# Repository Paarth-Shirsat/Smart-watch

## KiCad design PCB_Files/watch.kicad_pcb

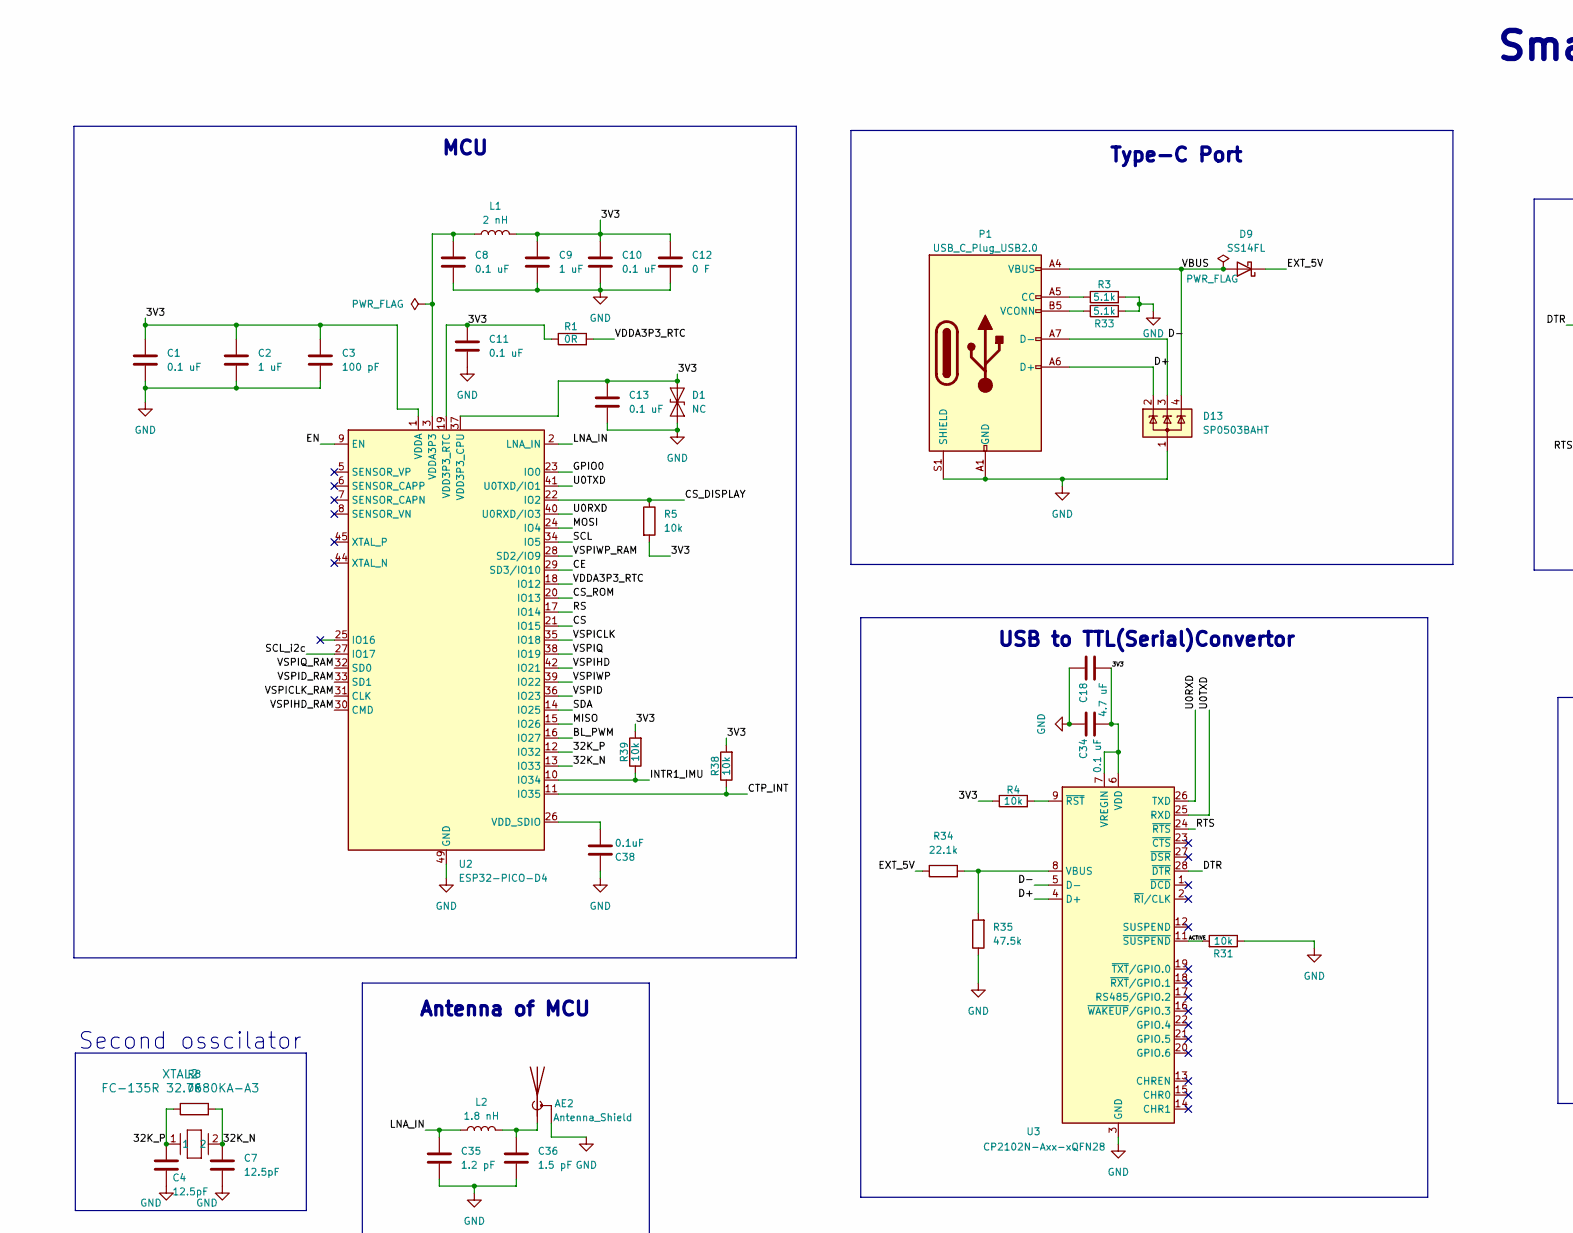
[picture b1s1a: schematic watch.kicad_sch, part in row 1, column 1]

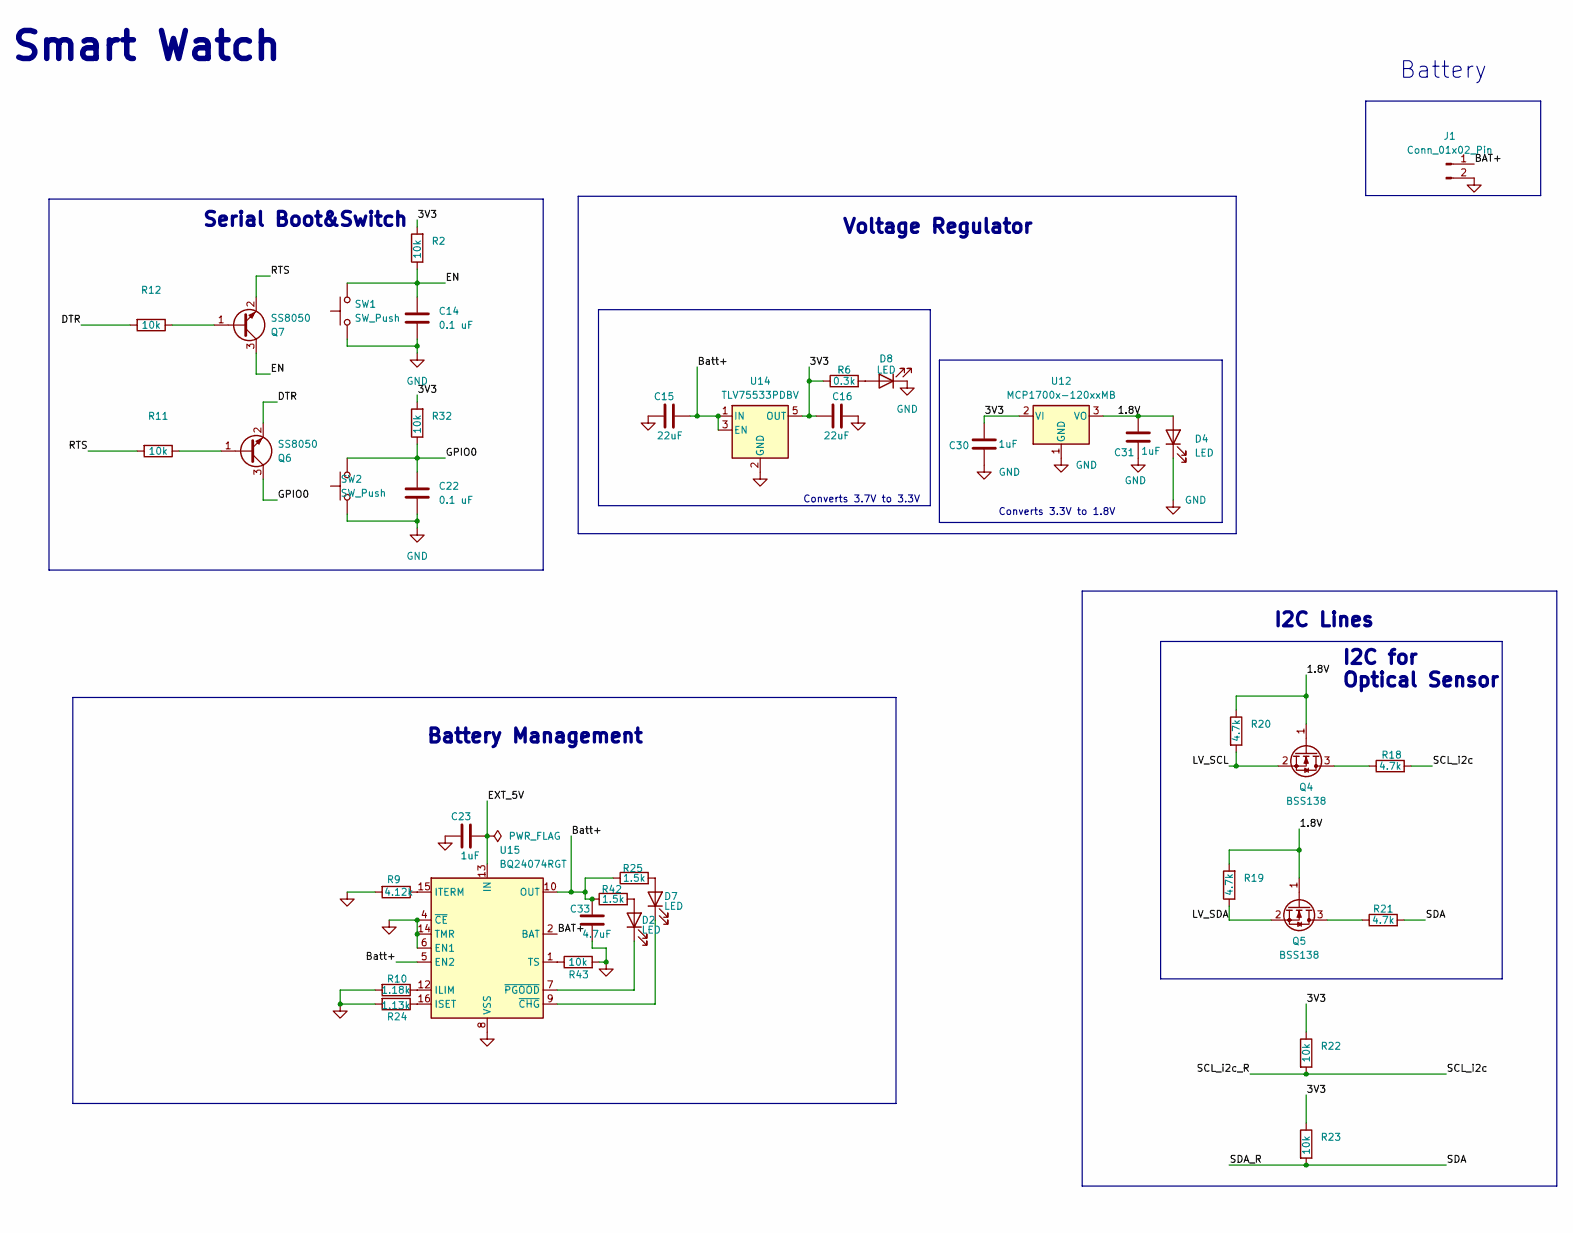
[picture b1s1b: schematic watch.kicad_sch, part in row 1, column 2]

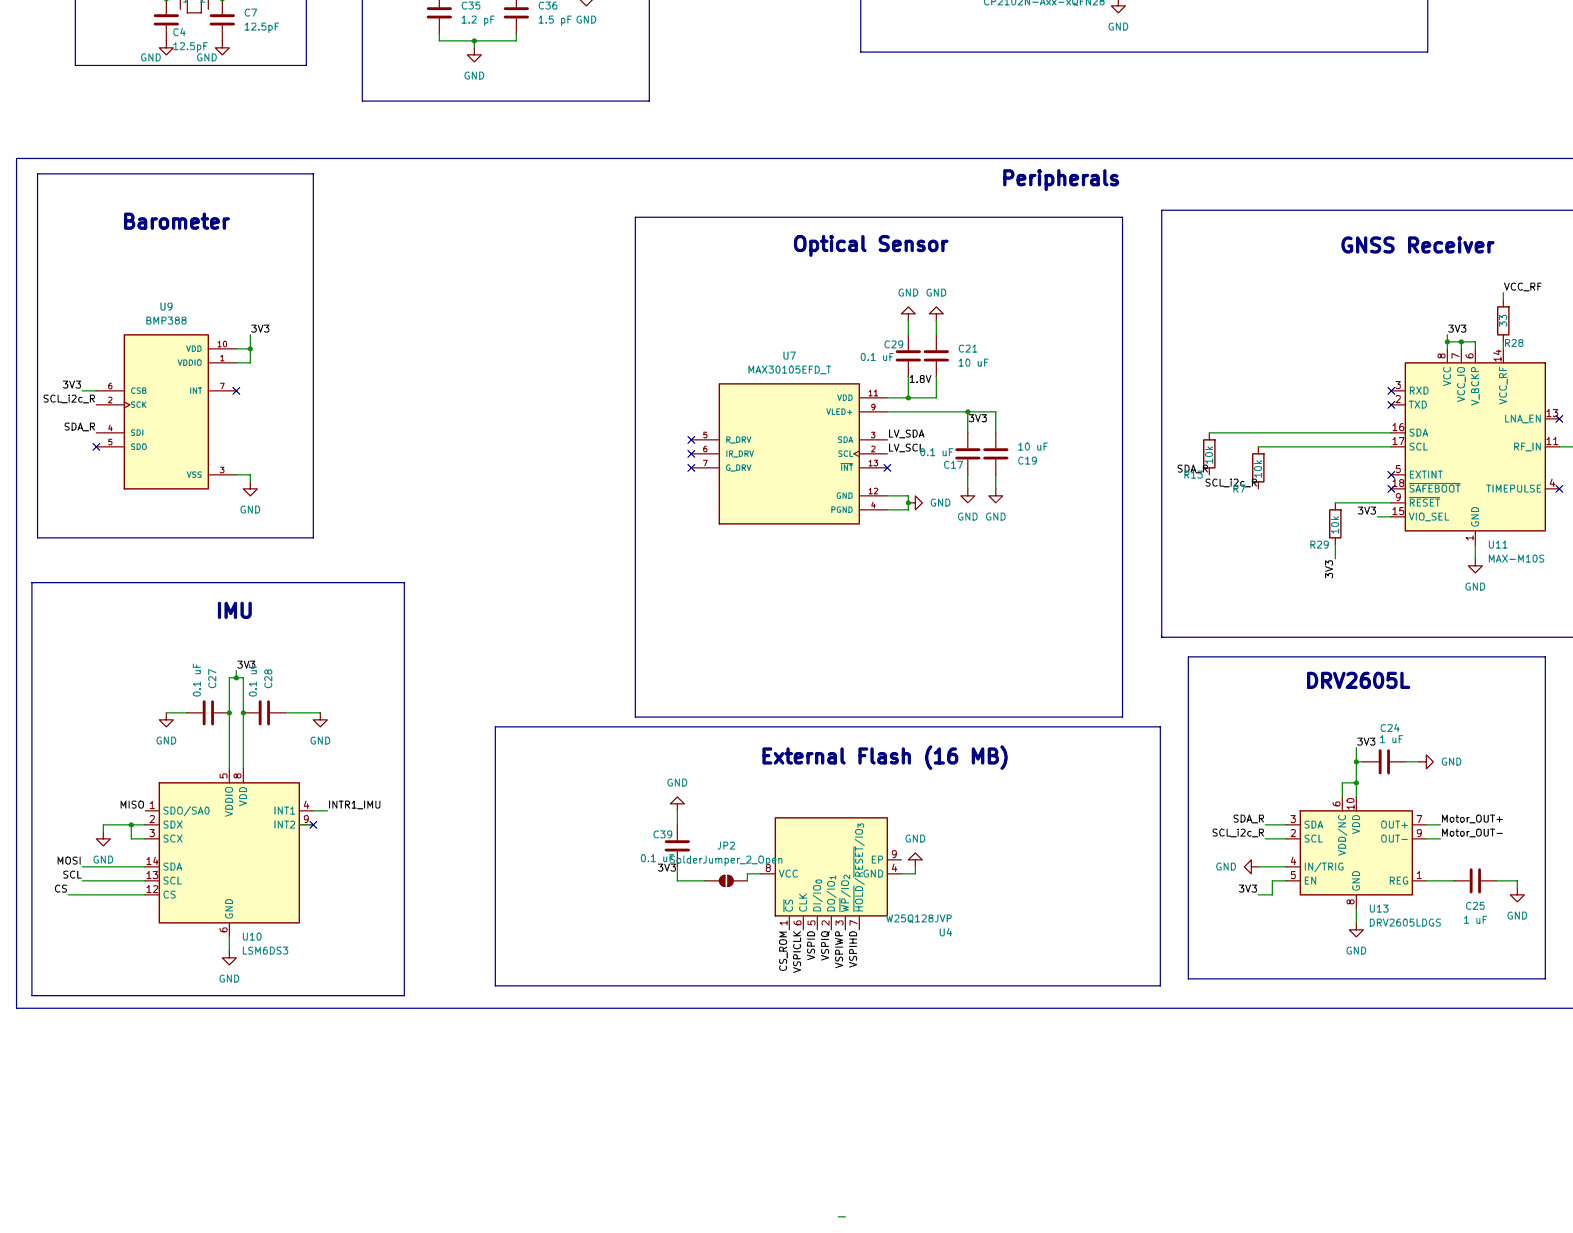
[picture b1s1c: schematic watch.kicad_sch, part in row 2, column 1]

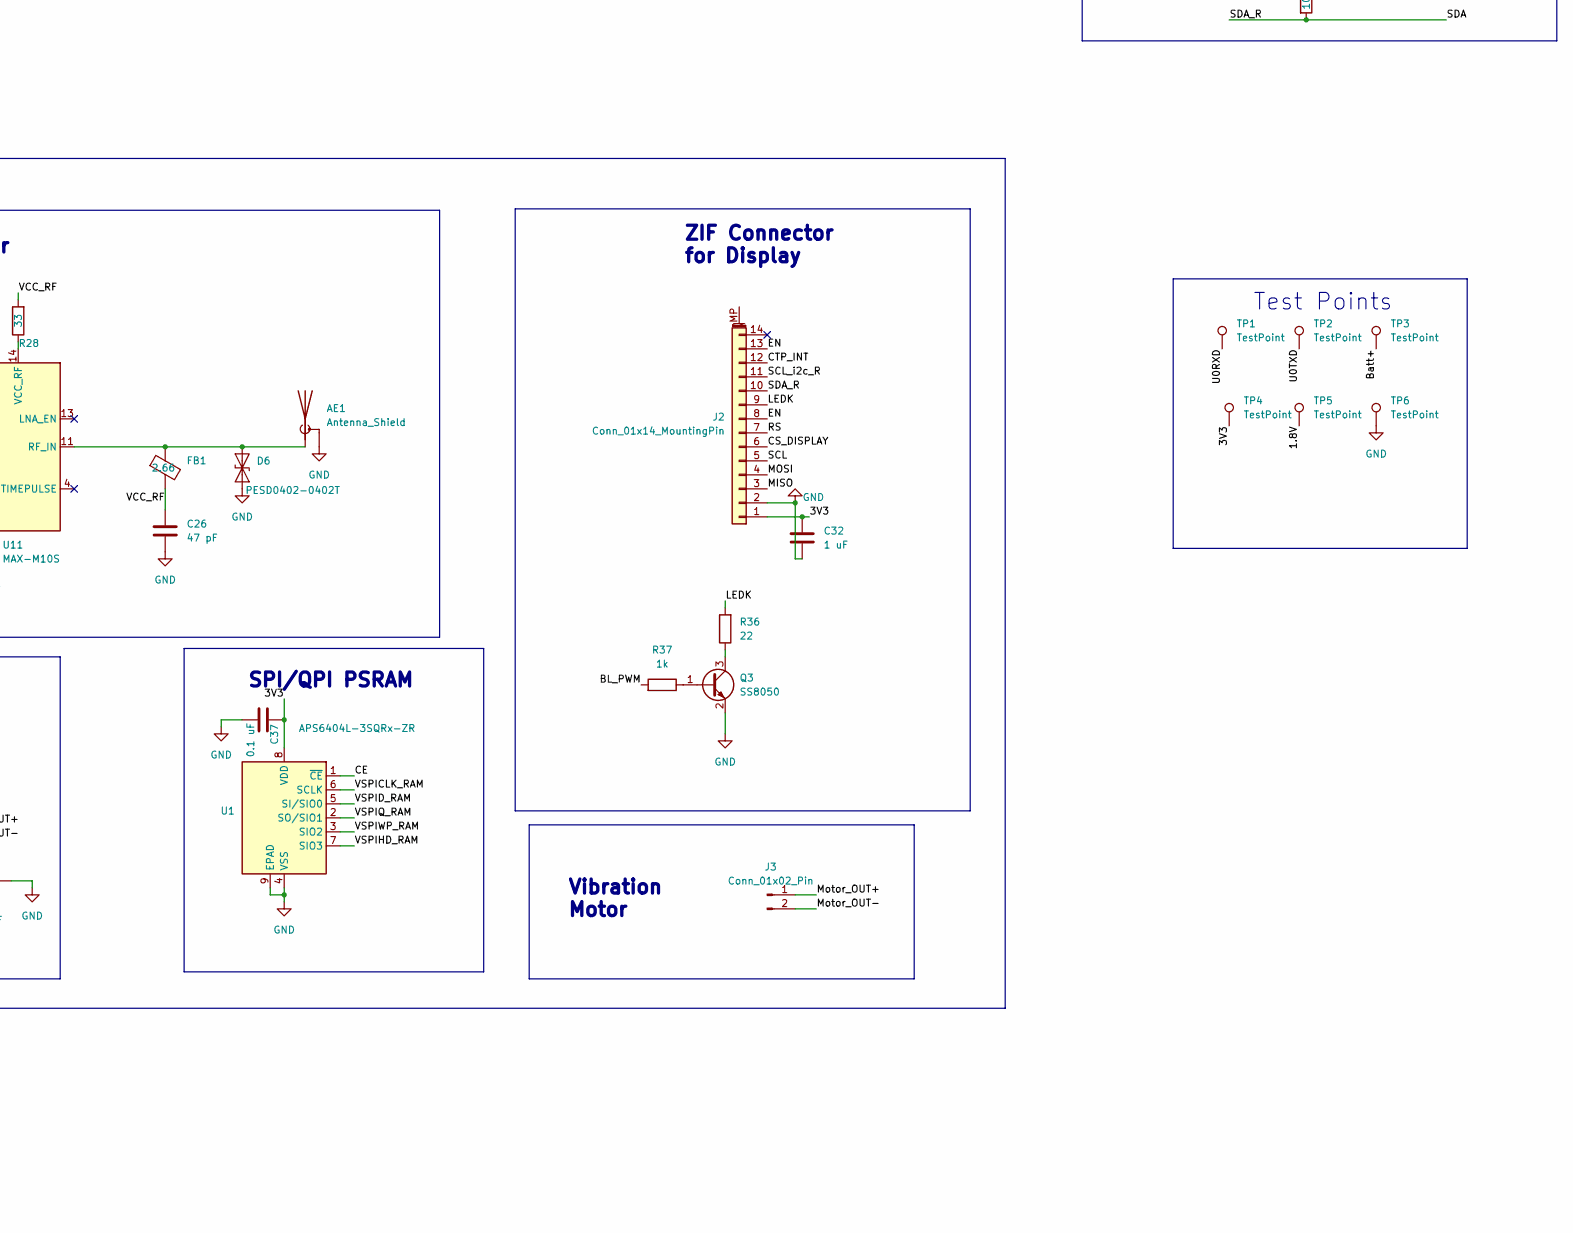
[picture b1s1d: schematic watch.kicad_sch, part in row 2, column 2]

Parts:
AE1, AE2: Antenna_Shield; XCVR_NN03-320
C1, C8, C10, C11, C13, C14, C17, C22, C27, C28, C29, C34, C37, C39: 0.1 uF; C_0603_1608Metric
C2, C9, C24, C25, C32: 1 uF; C_0603_1608Metric
C3: 100 pF; C_0603_1608Metric
C4, C7: 12.5pF; C_0603_1608Metric
C12: 0 F; C_0603_1608Metric
C15, C16: 22uF; C_0603_1608Metric
C18: 4.7 uF; C_0603_1608Metric
C19, C21: 10 uF; C_0603_1608Metric
C23, C30, C31: 1uF; C_0603_1608Metric
C26: 47 pF; C_0402_1005Metric
C33: 4.7uF; C_0603_1608Metric
C35: 1.2 pF; C_0603_1608Metric
C36: 1.5 pF; C_0603_1608Metric
C38: 0.1uF; C_0603_1608Metric
D1: NC; C_0603_1608Metric
D2, D4, D7, D8: LED; LED_0603_1608Metric
D6: PESD0402-0402T; D_SOD-923
D9: SS14FL; D_SOD-123
D13: SP0503BAHT; SOT-143
FB1: 2.66; L_0402_1005Metric
J1: Conn_01x02_Pin; PinHeader_1x02_P1.00mm_Vertical
J2: Conn_01x14_MountingPin; HRS_FH34SRJ-14S-0.5SH_50_
J3: Conn_01x02_Pin; D_0603_1608Metric
JP2: SolderJumper_2_Open; R_0402_1005Metric
L1: 2 nH; L_0603_1608Metric
L2: 1.8 nH; L_0603_1608Metric
P1: USB_C_Plug_USB2.0; USB_C_Receptacle_GCT_USB4105-xx-A_16P_TopMnt_Horizontal
Q3, Q6, Q7: SS8050; SOT-23
Q4, Q5: BSS138; SOT-23
R1, R8: 0R; R_0603_1608Metric
R2, R4, R5, R7, R11, R12, R13, R22, R23, R29, R31, R32, R38, R39, R43: 10k; R_0603_1608Metric
R3, R33: 5.1k; R_0603_1608Metric
R6: 0.3k; R_0603_1608Metric
R9: 4.12k; R_0603_1608Metric
R10: 1.18k; R_0603_1608Metric
R18, R19, R20, R21: 4.7k; R_0603_1608Metric
R24: 1.13k; R_0603_1608Metric
R25, R42: 1.5k; R_0603_1608Metric
R28: 33; R_0402_1005Metric
R34: 22.1k; R_0603_1608Metric
R35: 47.5k; R_0603_1608Metric
R36: 22; R_0603_1608Metric
R37: 1k; R_0603_1608Metric
SW1, SW2: SW_Push; SW_Push_SPST_NO_Alps_SKRK
TP1, TP2, TP3, TP4, TP5, TP6: TestPoint; TestPoint_Pad_D1.0mm
U1: APS6404L-3SQRx-ZR; Winbond_USON-8-1EP_3x2mm_P0.5mm_EP0.2x1.6mm
U2: ESP32-PICO-D4; QFN-48-1EP_7x7mm_P0.5mm_EP5.3x5.3mm
U3: CP2102N-Axx-xQFN28; QFN-28-1EP_5x5mm_P0.5mm_EP3.35x3.35mm
U4: W25Q128JVP; WSON-8-1EP_6x5mm_P1.27mm_EP3.4x4.3mm
U7: MAX30105EFD_T; 14-OESIP
U9: BMP388; PQFN50P200X200X80-10N
U10: LSM6DS3; LGA-14_3x2.5mm_P0.5mm_LayoutBorder3x4y
U11: MAX-M10S; ublox_MAX
U12: MCP1700x-120xxMB; SOT-89-3
U13: DRV2605LDGS; VSSOP-10_3x3mm_P0.5mm
U14: TLV75533PDBV; SOT-23-5
U15: BQ24074RGT; VQFN-16-1EP_3x3mm_P0.5mm_EP1.6x1.6mm
XTAL2: FC-135R 32.7680KA-A3; XTAL_KA-A3_EPS

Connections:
/1.8V: C21.2, C29.2, C31.2, D4.2 (A), Q4.1 (G), Q5.1 (G), R19.2, R20.1, TP5.1, U7.11 (VDD), U12.3 (VO)
/3V3: C1.1, C2.1, C3.1, C9.1, C10.1, C11.1, C12.1, C13.1, C16.1, C17.2, C18.2, C19.2, C24.1, C27.1, C28.2, C30.2, C32.1, C34.2, C37.1, C39.2, D1.2 (A2), J2.1, JP2.2 (B), L1.2, R1.1, R2.2, R4.1, R5.2, R6.1, R22.1, R23.1, R29.1, R32.2, R38.2, R39.2, TP4.1, U1.8 (VDD), U2.1 (VDDA), U2.19 (VDD3P3_RTC), U2.37 (VDD3P3_CPU), U2.43 (VDDA), U2.46 (VDDA), U3.6 (VDD), U3.7 (VREGIN), U7.9 (VLED+), U9.1 (VDDIO), U9.6 (CSB), U9.10 (VDD), U10.5 (VDDIO), U10.8 (VDD), U11.6 (V_BCKP), U11.7 (VCC_IO), U11.8 (VCC), U11.15 (VIO_SEL), U12.2 (VI), U13.5 (EN), U13.6 (VDD/NC), U13.10 (VDD), U14.5 (OUT)
/32K_N: C7.1, R8.2, U2.13 (IO33), XTAL2.2
/32K_P: C4.1, R8.1, U2.12 (IO32), XTAL2.1
/ACTIVE: R31.2, U3.11 (~SUSPEND)
/BAT+: J1.1, U15.2 (BAT), U15.3 (BAT)
/BL_PWM: R37.2, U2.16 (IO27)
/Batt+: C15.1, C33.1, R25.1, R42.1, TP3.1, U14.1 (IN), U14.3 (EN), U15.5 (EN2), U15.10 (OUT), U15.11 (OUT)
/CE: U1.1 (~CE), U2.29 (SD3/IO10)
/CS: U2.21 (IO15), U10.12 (CS)
/CS_DISPLAY: J2.6, R5.1, U2.22 (IO2)
/CS_ROM: U2.20 (IO13), U4.1 (~CS)
/CTP_INT: J2.12, R38.1, U2.11 (IO35)
/D+: D13.2 (K), P1.A6 (D+), U3.4 (D+)
/D-: D13.3 (K), P1.A7 (D-), U3.5 (D-)
/DTR: Q6.2 (E), R12.2, U3.28 (~DTR)
/EN: C14.1, J2.8, J2.13, Q7.3 (C), R2.1, SW1.2, U2.9 (EN)
/EXT_5V: C23.1, D9.1 (K), R34.1, U15.13 (IN)
/GPIO0: C22.1, Q6.3 (C), R32.1, SW2.2, U2.23 (IO0)
/INTR1_IMU: R39.1, U2.10 (IO34), U10.4 (INT1)
/LEDK: J2.9, R36.2
/LNA_IN: C35.1, L2.1, U2.2 (LNA_IN)
/LV_SCL: Q4.2 (S), R20.2, U7.2 (SCL)
/LV_SDA: Q5.2 (S), R19.1, U7.3 (SDA)
/MISO: J2.3, U2.15 (IO26), U10.1 (SDO/SA0)
/MOSI: J2.4, U2.24 (IO4), U10.14 (SDA)
/Motor_OUT+: J3.1, U13.7 (OUT+)
/Motor_OUT-: J3.2, U13.9 (OUT-)
/RS: J2.7, U2.17 (IO14)
/RTS: Q7.2 (E), R11.2, U3.24 (~RTS)
/SCL: J2.5, U2.34 (IO5), U10.13 (SCL)
/SCL_i2c: J2.11, R7.1, R18.2, R22.2, U2.27 (IO17), U9.2 (SCK), U13.2 (SCL)
/SDA: J2.10, R13.1, R21.2, R23.2, U2.14 (IO25), U9.4 (SDI), U13.3 (SDA)
/U0RXD: TP1.1, U2.40 (U0RXD/IO3), U3.26 (TXD)
/U0TXD: TP2.1, U2.41 (U0TXD/IO1), U3.25 (RXD)
/VBUS: D9.2 (A), D13.4 (K), P1.A4 (VBUS), P1.A9 (VBUS), P1.B4 (VBUS), P1.B9 (VBUS)
/VCC_RF: C26.1, FB1.2, R28.2
/VDDA3P3_RTC: R1.2, U2.18 (IO12)
/VSPICLK: U2.35 (IO18), U4.6 (CLK)
/VSPICLK_RAM: U1.6 (SCLK), U2.31 (CLK)
/VSPID: U2.36 (IO23), U4.5 (DI/IO_{0})
/VSPID_RAM: U1.5 (SI/SIO0), U2.33 (SD1)
/VSPIHD: U2.42 (IO21), U4.7 (~HOLD/~RESET/IO_{3})
/VSPIHD_RAM: U1.7 (SIO3), U2.30 (CMD)
/VSPIQ: U2.38 (IO19), U4.2 (DO/IO_{1})
/VSPIQ_RAM: U1.2 (SO/SIO1), U2.32 (SD0)
/VSPIWP: U2.39 (IO22), U4.3 (~WP/IO_{2})
/VSPIWP_RAM: U1.3 (SIO2), U2.28 (SD2/IO9)
GND: AE1.2 (Shield), AE2.2 (Shield), C1.2, C2.2, C3.2, C4.2, C7.2, C8.2, C9.2, C10.2, C11.2, C12.2, C13.2, C14.2, C15.2, C16.2, C17.1, C18.1, C19.1, C21.1, C22.2, C23.2, C24.2, C25.2, C26.2, C27.2, C28.1, C29.1, C30.1, C31.1, C32.2, C33.2, C34.1, C35.2, C36.2, C37.2, C38.1, C39.1, D1.1 (A1), D4.1 (K), D6.1 (A1), D8.1 (K), D13.1 (A), J1.2, J2.2, P1.A1 (GND), P1.A12 (GND), P1.B1 (GND), P1.B12 (GND), P1.S1 (SHIELD), Q3.2 (E), R3.2, R9.2, R10.2, R24.2, R31.1, R33.2, R35.1, R43.2, SW1.1, SW2.1, TP6.1, U1.4 (VSS), U1.9 (EPAD), U2.49 (GND), U3.3 (GND), U3.29 (GND), U4.4 (GND), U7.4 (PGND), U7.12 (GND), U9.3 (VSS), U9.8 (VSS), U9.9 (VSS), U10.2 (SDX), U10.3 (SCX), U10.6 (GND), U10.7 (GND), U11.1 (GND), U11.10 (GND), U11.12 (GND), U12.1 (GND), U13.4 (IN/TRIG), U13.8 (GND), U14.2 (GND), U15.4 (~CE), U15.6 (EN1), U15.8 (VSS), U15.14 (TMR), U15.17 (VSS)
unnamed: AE1.3 (A), D6.2 (A2), FB1.1, U11.11 (RF_IN)
unnamed: AE2.3 (A), C36.1, L2.2
unnamed: C8.1, L1.1, U2.3 (VDDA3P3), U2.4 (VDDA3P3)
unnamed: D2.2 (A), R42.2
unnamed: D2.1 (K), U15.7 (~PGOOD)
unnamed: D7.2 (A), R25.2
unnamed: D7.1 (K), U15.9 (~CHG)
unnamed: D8.2 (A), R6.2
unnamed: JP2.1 (A), U4.8 (VCC)
unnamed: P1.A5 (CC), R3.1
unnamed: P1.B5 (VCONN), R33.1
unnamed: Q3.1 (B), R37.1
unnamed: Q3.3 (C), R36.1
unnamed: Q4.3 (D), R18.1
unnamed: Q5.3 (D), R21.1
unnamed: Q6.1 (B), R11.1
unnamed: Q7.1 (B), R12.1
unnamed: C38.2, U2.26 (VDD_SDIO)
unnamed: R34.2, R35.2, U3.8 (VBUS)
unnamed: R4.2, U3.9 (~RST)
unnamed: R7.2, U11.17 (SCL)
unnamed: R13.2, U11.16 (SDA)
unnamed: R28.1, U11.14 (VCC_RF)
unnamed: R29.2, U11.9 (~RESET)
unnamed: C25.1, U13.1 (REG)
unnamed: R10.1, U15.12 (ILIM)
unnamed: R24.1, U15.16 (ISET)
unnamed: R9.1, U15.15 (ITERM)
unnamed: R43.1, U15.1 (TS)

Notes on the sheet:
USB to TTL(Serial)Convertor
External Flash (16 MB)
DRV2605L
Second osscilator
Battery
Optical Sensor
Voltage Regulator
Smart Watch
ZIF Connector for Display
Converts 3.3V to 1.8V
MCU
I2C Lines
Battery Management
SPI/QPI PSRAM
GNSS Receiver
Type-C Port
Antenna of MCU
Vibration Motor
IMU
Serial Boot&Switch
Converts 3.7V to 3.3V
Peripherals
Test Points
Barometer
I2C for Optical Sensor

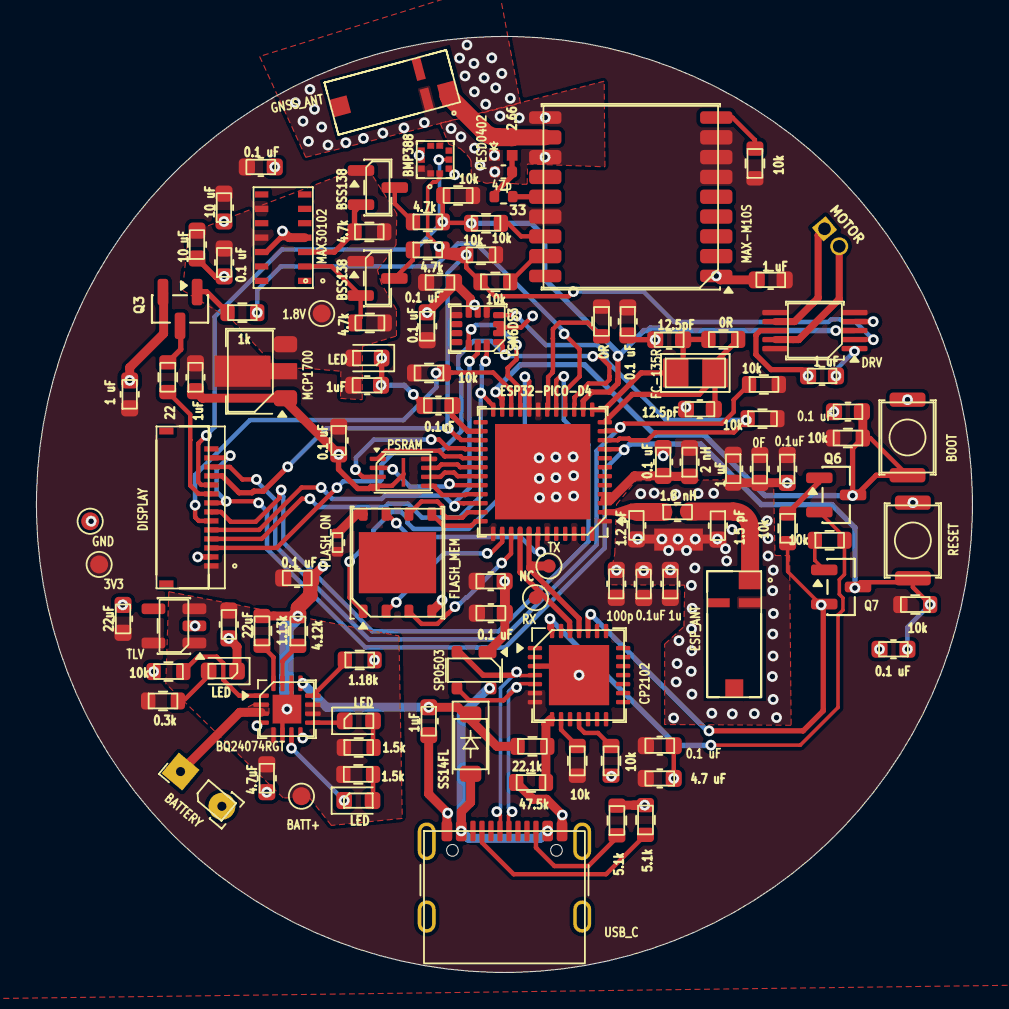
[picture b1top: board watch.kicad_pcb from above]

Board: 2 copper layers, 52.0 x 52.0 mm, 114 parts (0 on the bottom side), 78 nets.

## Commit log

2026-02-06 MCU schematics uploaded
2026-02-12 Schematics Updated
2026-02-12 Connected few peripherals and formatting
2026-02-18 Added Sensors
2026-02-19 Added Connections for Barometer, GNSS, Optical Sensor
2026-03-01 Schematics Completed
2026-03-16 Verified and corrected schematics
2026-03-21 Added custom footprint library and assigned footprints
2026-03-26 Set trace widths
2026-03-30 Added Firmware For MAX30102,LSM6DSO,max-m10s,bmp388
2026-04-01 Move custom footprints into PCB_Files and update library table
    Relocated footprints.pretty/ from project root into PCB_Files/ to keep all PCB-related assets together. Added new SOIC-8 footprint and updated fp-lib-table to point to the new path.
2026-04-01 Update PCB layout and project settings
2026-04-07 Changes in schematics
2026-04-07 Added new ZIF connector footprint and made changes in schematics
2026-04-08 Adding missing footprints and making cAD
2026-04-09 Added readme and assets
2026-04-10 changed place of some components and fixed antenna
2026-04-11 Making major changes in the schematic, added a external 40MHz crystal oscilator and did routing
2026-04-13 Made changes in schematic and routing
2026-04-14 Updating firmwares with more caliberated values and also integrating all the sensor readings
2026-04-25 Did changes in barometer
2026-04-25 First commit of restarting layout
2026-04-27 Did routing of ESP, USB, USB-to-TTL, RAM, Flash, Osscilator & PMIC
2026-04-27 Contiued routing
2026-04-28 Restarted routing
2026-04-30 Completed layout
2026-05-01 Did impedance matching of antennas
2026-05-01 Improving Antenna routing
2026-05-01 adding assets
2026-05-02 Added test firmware for GC9A01
2026-05-02 Initialised Zephyr with custom board definition
    This commit establishes the foundational firmware structure for the
    smartwatch project, migrating from ESP-IDF test firmware to a proper
    Zephyr RTOS application. Board will be updated to ESP32-PICO-D4 DTS
    when moving to final PCB.
2026-05-02 Fixed some routing
2026-05-02 zbus implementation
2026-05-09 Tested and added firmware for LSM6DSO
2026-05-22 Added firmware for BMP388
    Not tested.
